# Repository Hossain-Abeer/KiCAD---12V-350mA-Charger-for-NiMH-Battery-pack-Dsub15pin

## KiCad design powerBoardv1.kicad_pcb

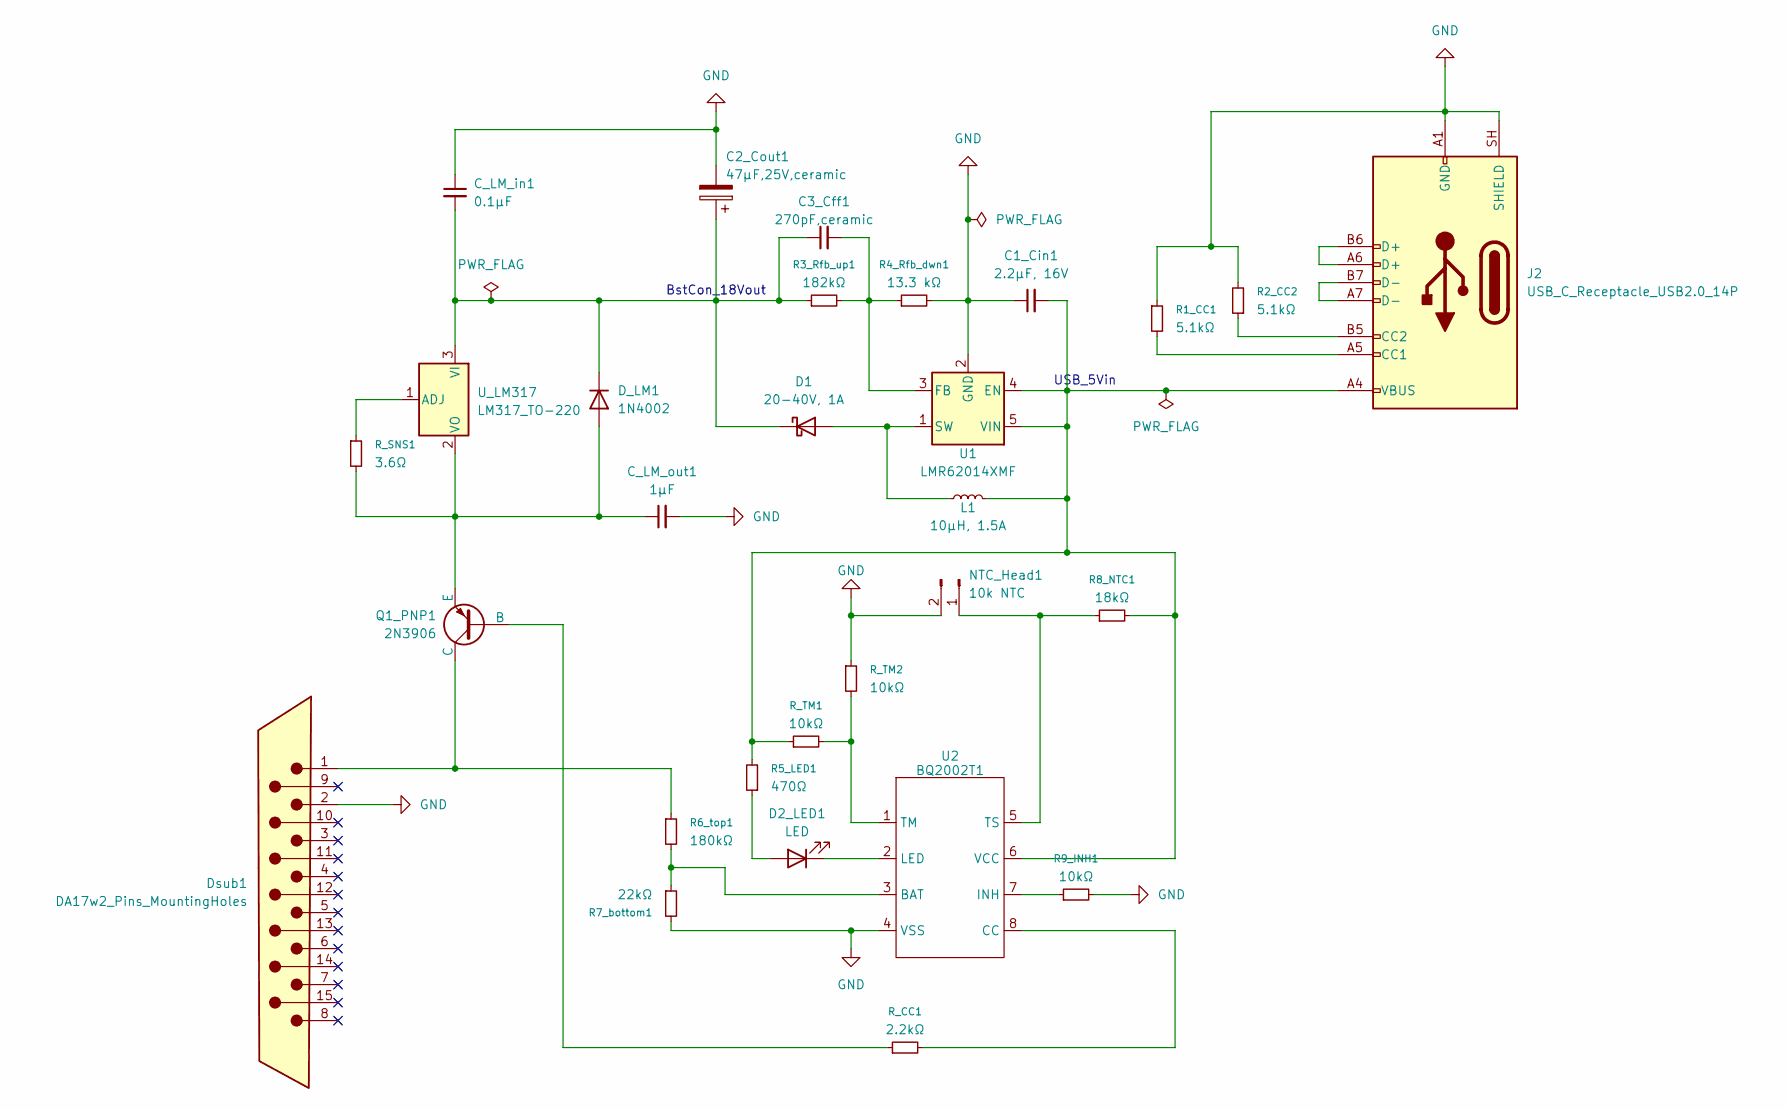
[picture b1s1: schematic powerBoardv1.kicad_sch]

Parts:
C1_Cin1: 2.2µF, 16V; C_1206_3216Metric_Pad1.33x1.80mm_HandSolder
C2_Cout1: 47µF,25V,ceramic; C_1210_3225Metric_Pad1.33x2.70mm_HandSolder
C3_Cff1: 270pF,ceramic; C_0805_2012Metric_Pad1.18x1.45mm_HandSolder
C_LM_in1: 0.1µF; C_0805_2012Metric_Pad1.18x1.45mm_HandSolder
C_LM_out1: 1µF; C_0805_2012Metric_Pad1.18x1.45mm_HandSolder
D1: 20-40V, 1A; D_DO-41_SOD81_P10.16mm_Horizontal
D2_LED1: LED; LED_D5.0mm
D_LM1: 1N4002; D_DO-41_SOD81_P10.16mm_Horizontal
Dsub1: DA17w2_Pins_MountingHoles; CONN_FM17W2P1-K120_MOL
J2: USB_C_Receptacle_USB2.0_14P; USB_C_Receptacle_GCT_USB4105-xx-A_16P_TopMnt_Horizontal
L1: 10µH, 1.5A; L_Axial_L9.5mm_D4.0mm_P15.24mm_Horizontal_Fastron_SMCC
NTC_Head1: 10k NTC; PinHeader_1x02_P2.54mm_Vertical
Q1_PNP1: 2N3906; TO-92_Inline
R1_CC1, R2_CC2: 5.1kΩ; R_Axial_DIN0207_L6.3mm_D2.5mm_P10.16mm_Horizontal
R3_Rfb_up1: 182kΩ; R_Axial_DIN0207_L6.3mm_D2.5mm_P10.16mm_Horizontal
R4_Rfb_dwn1: 13.3 kΩ; R_Axial_DIN0207_L6.3mm_D2.5mm_P10.16mm_Horizontal
R5_LED1: 470Ω; R_Axial_DIN0207_L6.3mm_D2.5mm_P10.16mm_Horizontal
R6_top1: 180kΩ; R_Axial_DIN0207_L6.3mm_D2.5mm_P10.16mm_Horizontal
R7_bottom1: 22kΩ; R_Axial_DIN0207_L6.3mm_D2.5mm_P10.16mm_Horizontal
R8_NTC1: 18kΩ; R_Axial_DIN0207_L6.3mm_D2.5mm_P10.16mm_Horizontal
R9_INH1: 10kΩ; R_Axial_DIN0207_L6.3mm_D2.5mm_P10.16mm_Horizontal
R_CC1: 2.2kΩ; R_Axial_DIN0207_L6.3mm_D2.5mm_P10.16mm_Horizontal
R_SNS1: 3.6Ω; R_Axial_DIN0207_L6.3mm_D2.5mm_P10.16mm_Horizontal
R_TM1, R_TM2: 10kΩ; R_Axial_DIN0207_L6.3mm_D2.5mm_P10.16mm_Horizontal
U1: LMR62014XMF; SOT-23-5_HandSoldering
U2: BQ2002T1; SOIC-8_3.9x4.9mm_P1.27mm
U_LM317: LM317_TO-220; TO-220-3_Vertical

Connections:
GND: C1_Cin1.1, C2_Cout1.2, C_LM_in1.1, C_LM_out1.2, Dsub1.2, J2.A1 (GND), J2.A12 (GND), J2.B1 (GND), J2.B12 (GND), J2.SH (SHIELD), NTC_Head1.2, R1_CC1.1, R2_CC2.2, R4_Rfb_dwn1.2, R7_bottom1.2, R9_INH1.2, R_TM2.1, U1.2 (GND), U2.4 (VSS)
unnamed: D1.2 (A), L1.1, U1.1 (SW)
unnamed: C2_Cout1.1, C3_Cff1.1, C_LM_in1.2, D1.1 (K), D_LM1.1 (K), R3_Rfb_up1.1, U_LM317.3 (VI)
unnamed: D2_LED1.2 (A), R5_LED1.1
unnamed: D2_LED1.1 (K), U2.2 (LED)
unnamed: C_LM_out1.1, D_LM1.2 (A), Q1_PNP1.3 (E), R_SNS1.2, U_LM317.2 (VO)
unnamed: J2.A5 (CC1), R1_CC1.2
unnamed: J2.B5 (CC2), R2_CC2.1
unnamed: J2.A6 (D+), J2.B6 (D+)
unnamed: J2.A7 (D-), J2.B7 (D-)
unnamed: NTC_Head1.1, R8_NTC1.1, U2.5 (TS)
unnamed: Q1_PNP1.2 (B), R_CC1.1
unnamed: Dsub1.1, Q1_PNP1.1 (C), R6_top1.1
unnamed: C1_Cin1.2, J2.A4 (VBUS), J2.A9 (VBUS), J2.B4 (VBUS), J2.B9 (VBUS), L1.2, R5_LED1.2, R8_NTC1.2, R_TM1.1, U1.4 (EN), U1.5 (VIN), U2.6 (VCC)
unnamed: C3_Cff1.2, R3_Rfb_up1.2, R4_Rfb_dwn1.1, U1.3 (FB)
unnamed: R6_top1.2, R7_bottom1.1, U2.3 (BAT)
unnamed: R_CC1.2, U2.8 (CC)
unnamed: R9_INH1.1, U2.7 (INH)
unnamed: R_TM1.2, R_TM2.2, U2.1 (TM)
unnamed: R_SNS1.1, U_LM317.1 (ADJ)

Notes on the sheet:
USB_5Vin
BstCon_18Vout

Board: 2 copper layers, 29 parts (0 on the bottom side), 20 nets, no tracks yet.

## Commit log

2026-05-07 files uploaded
    on this iteration, all the subsystems of the charger has been connected with the Dsub port left out unconnected, as the official datasheet of the battery pack (with female Dsub) wasn't provided. Dsub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
2026-05-12 network is complete, all pins are connected
    but footprint of all the components & subcomponents are not yet assigned or validated.
2026-05-17 footprints assigned
    this iteration has footprints assigned. Dsub-17w2's footprint for kicad v6 is downloaded from digikey, used and also uploaded in the repo
2026-05-28 the '_sch' file contains Francesco's revisions
    Mr Franscesco's revision regarding:
    1. the positioning of the NTC being on the battery instead of the PCB.
    2. the change in R_CC. This R_CC is connected to the node of BQ2002T pin CC. To lower the current coming into this pin from the PNP
2026-05-28 PCBv1
    No network, screw holes
2026-06-01 PCBv1
    This PCB is ready for prototyping. 100mm x 70.5mm
    Component placement is EMC optimised, traces are widened aptly, dual layer copper pour, 4 2.5mm drill holes, silkscreen tags. DRC ran without errors.
2026-06-01 export files
    Export files - Gerber, drill, BOM & PDF files
